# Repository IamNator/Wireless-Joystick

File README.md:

# Wireless-Joystick

Building a wireless joystick from scratch

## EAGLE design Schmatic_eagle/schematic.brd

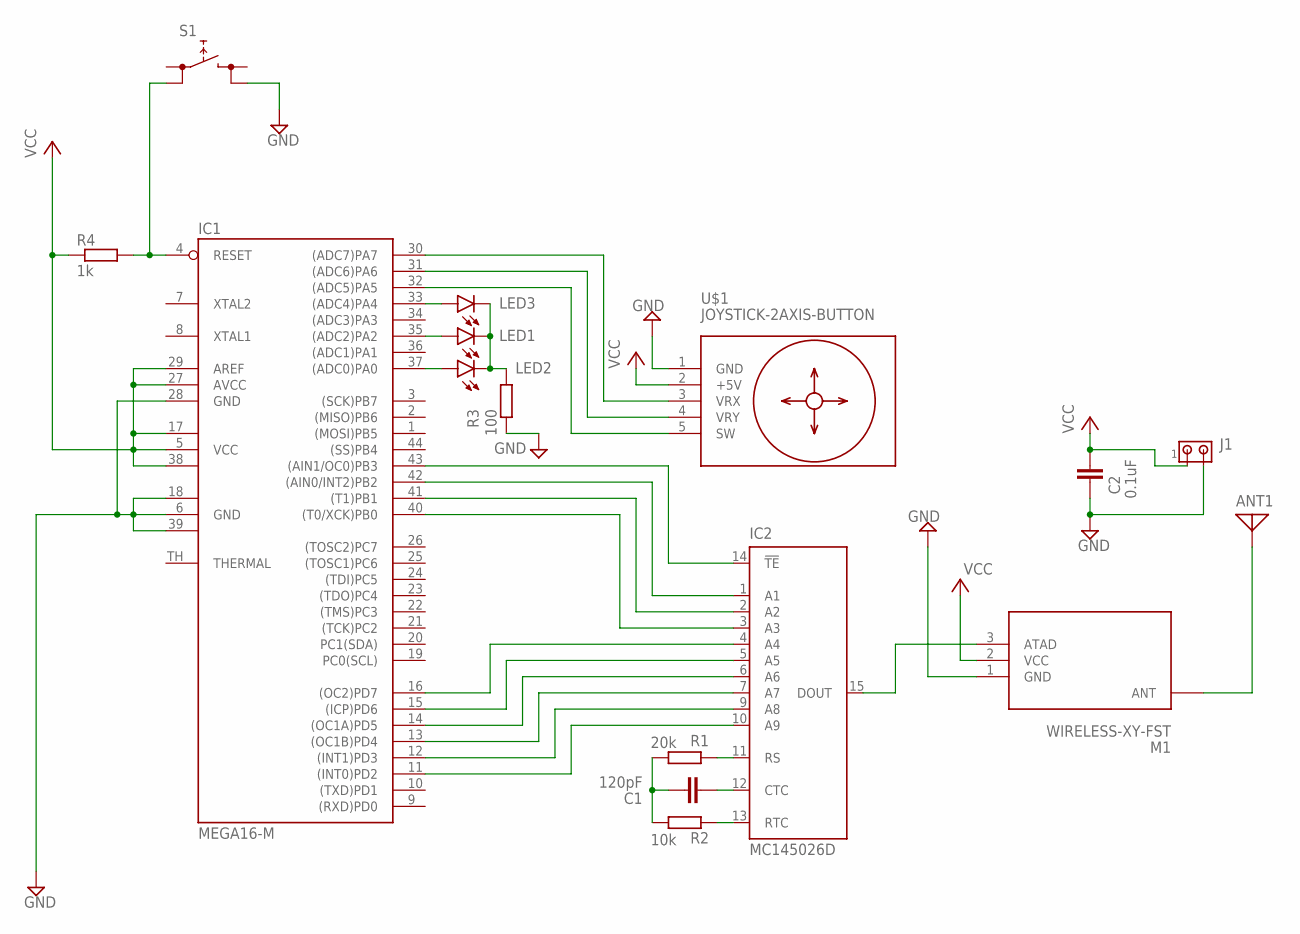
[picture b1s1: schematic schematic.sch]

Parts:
ANT1: ANTENNA; PAD-01
C1: 120pF; C2.5-3
C2: 0.1uF; C2.5-3
IC1: MEGA16-M; MLF44-TH
IC2: MC145026D; SO16
J1: MTA02-100; 10X02MTA
LED1, LED2, LED3: LEDCHIPLED_1206; CHIPLED_1206
M1: WIRELESS-XY-FST
R1: 20k; M0805
R2: 10k; R0805
R3: 100; M0805
R4: 1k; R0805
S1: REKN
U$1: JOYSTICK-2AXIS-BUTTON

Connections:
GND: C2.1, IC1.6 (GND), IC1.18 (GND1), IC1.28 (GND), IC1.39 (GND2), J1.2, M1.1 (GND), R3.2, S1.1B (1), U$1.1 (GND)
unnamed: IC1.30 ((ADC7)PA7), U$1.3 (VRX)
unnamed: IC1.31 ((ADC6)PA6), U$1.4 (VRY)
unnamed: IC1.32 ((ADC5)PA5), U$1.5 (SW)
unnamed: IC2.11 (RS), R1.1
unnamed: C1.2, IC2.12 (CTC)
unnamed: IC2.13 (RTC), R2.1
unnamed: C1.1, R1.2, R2.2
unnamed: IC2.15 (DOUT), M1.3 (ATAD)
unnamed: ANT1.1, M1.ANT
unnamed: IC1.13 ((OC1B)PD4), IC2.7 (A7)
unnamed: IC1.14 ((OC1A)PD5), IC2.6 (A6)
unnamed: IC1.15 ((ICP)PD6), IC2.5 (A5)
unnamed: IC1.11 ((INT0)PD2), IC2.10 (A9)
unnamed: IC1.12 ((INT1)PD3), IC2.9 (A8)
unnamed: IC1.16 ((OC2)PD7), IC2.4 (A4)
unnamed: IC1.4 (RESET), R4.2, S1.0B (0)
unnamed: IC1.43 ((AIN1/OC0)PB3), IC2.14 (!TE)
unnamed: IC1.42 ((AIN0/INT2)PB2), IC2.1 (A1)
unnamed: IC1.41 ((T1)PB1), IC2.2 (A2)
unnamed: IC1.40 ((T0/XCK)PB0), IC2.3 (A3)
unnamed: IC1.33 ((ADC4)PA4), LED3.A
unnamed: IC1.35 ((ADC2)PA2), LED1.A
unnamed: IC1.37 ((ADC0)PA0), LED2.A
unnamed: LED1.C, LED2.C, LED3.C, R3.1
VCC: C2.2, IC1.5 (VCC), IC1.17 (VCC1), IC1.27 (AVCC), IC1.29 (AREF), IC1.38 (VCC2), J1.1, M1.2 (VCC), R4.1, U$1.2 (+5V)
VDD: IC2.16 (VDD)
VSS: IC2.8 (VSS)

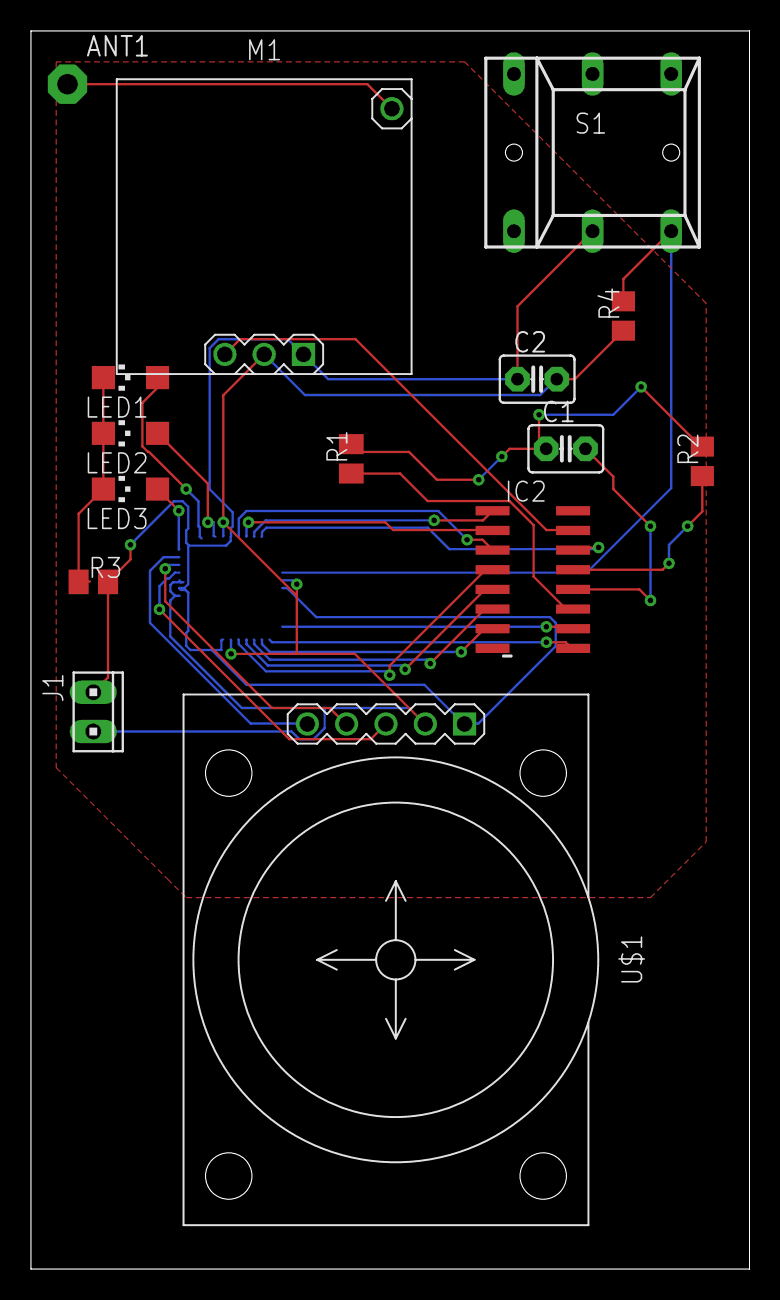
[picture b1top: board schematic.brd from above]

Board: 2 copper layers, 46.4 x 80.0 mm, 16 parts (1 on the bottom side), 26 nets.

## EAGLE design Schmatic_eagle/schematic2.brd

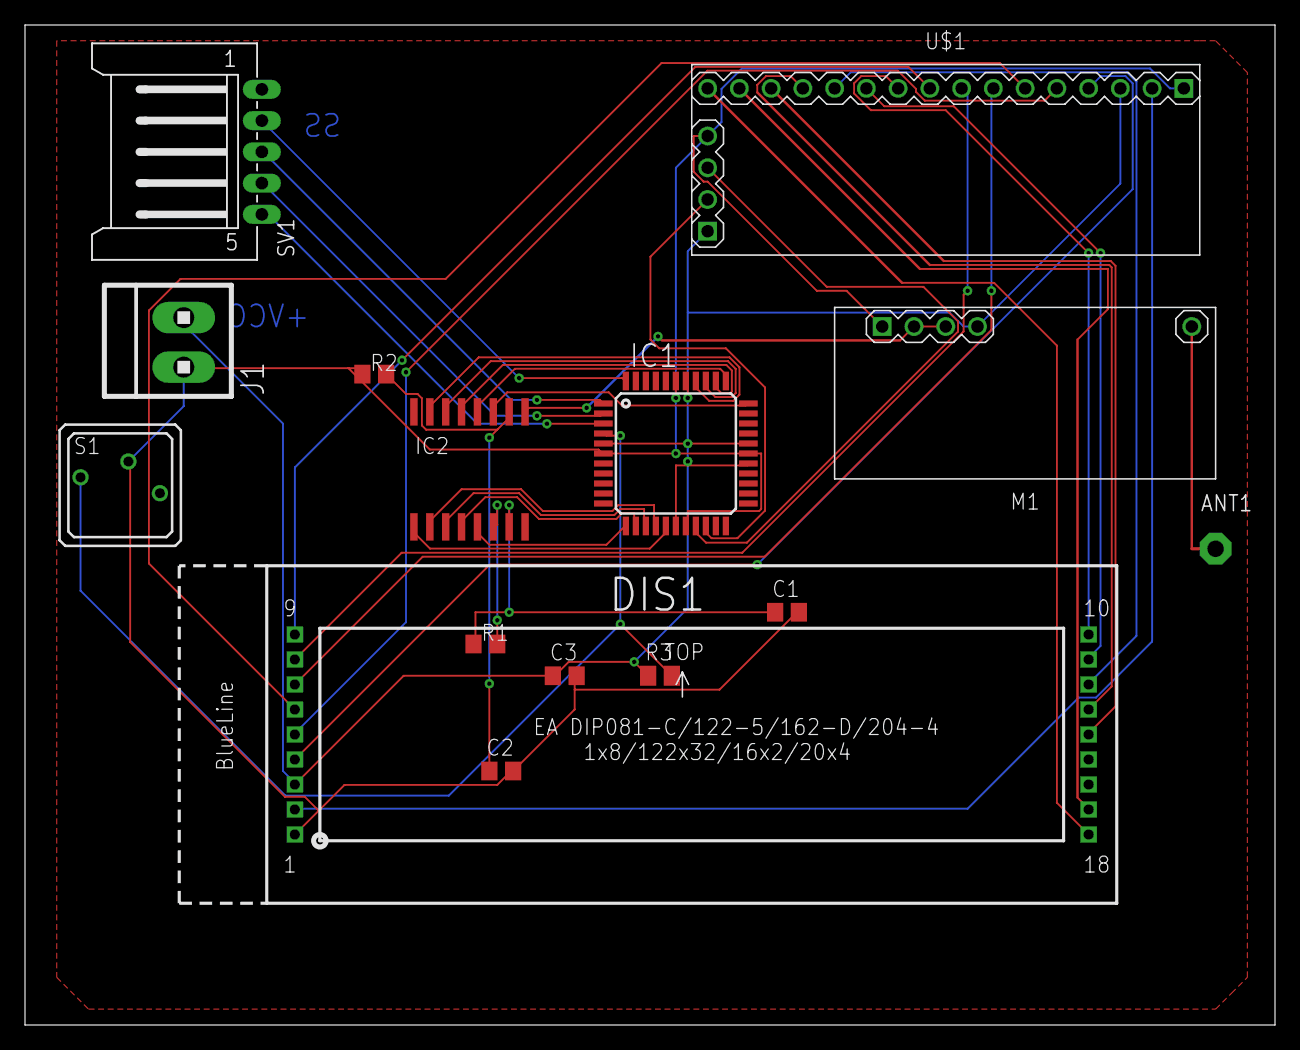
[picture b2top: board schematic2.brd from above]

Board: 2 copper layers, 100.0 x 80.0 mm, 15 parts (0 on the bottom side), 38 nets.

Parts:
ANT1: PAD-01
C1: 470pF; C0805
C2: 910pF; C0805
C3: 0.1uF; C0805
DIS1: EA_DIP
IC1: MEGA16-A; TQFP44
IC2: MC145027DW; SO16W
J1: 1X2MTA
M1: WIRELESS-XY-MK-5V
R1: 10k; R0805
R2: 100k; R0805
R3: 1k; M0805
S1: RDT1034
SV1: L05P
U$1: LCD-I2C-CONVERTER

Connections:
GND: C1.2, C2.2, C3.2, DIS1.1, IC1.6, IC1.18, IC1.28, IC1.39, J1.2, M1.1, R2.1, S1.B, U$1.J1.4, U$1.J2.1
unnamed: IC1.16, IC2.1
unnamed: IC1.15, IC2.2
unnamed: IC1.14, IC2.3
unnamed: IC1.13, IC2.4
unnamed: IC1.12, IC2.5
unnamed: IC1.35, IC2.13
unnamed: IC1.37, IC2.15
unnamed: IC1.36, IC2.14
unnamed: IC1.34, IC2.12
unnamed: IC2.6, R1.2
unnamed: C1.1, IC2.7, R1.1
unnamed: C2.1, IC2.10, R2.2
unnamed: IC2.9, M1.2, M1.3
unnamed: IC1.3, SV1.5
unnamed: ANT1.1, M1.ANT
unnamed: IC1.2, SV1.4
unnamed: IC1.1, SV1.3
unnamed: IC1.44, SV1.2
unnamed: IC1.4, R3.2, S1.A1
unnamed: IC1.33, IC2.11
unnamed: IC1.19, U$1.J1.3
unnamed: IC1.20, U$1.J1.2
unnamed: DIS1.7, U$1.J2.7
unnamed: DIS1.4, U$1.J2.4
unnamed: DIS1.5, U$1.J2.5
unnamed: DIS1.6, U$1.J2.6
unnamed: DIS1.8, U$1.J2.8
unnamed: DIS1.9, U$1.J2.9
unnamed: DIS1.10, U$1.J2.10
unnamed: DIS1.11, U$1.J2.11
unnamed: DIS1.12, U$1.J2.12
unnamed: DIS1.2, U$1.J2.2
unnamed: DIS1.13, U$1.J2.13
unnamed: DIS1.17, U$1.J2.15
unnamed: DIS1.18, U$1.J2.16
unnamed: DIS1.14, U$1.J2.14
VCC: C3.1, DIS1.3, IC1.5, IC1.17, IC1.27, IC1.29, IC1.38, J1.1, M1.4, R3.1, U$1.J1.1, U$1.J2.3

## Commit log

2019-11-07 adding aschematic
2019-11-07 Removing c files
2019-11-07 adding schematric_eagle directory
2019-11-07 updated Schematic
2019-11-07 Schematic updates
2019-11-07 Schematic updtes
2019-11-08 Schematic update
2019-11-08 Schematic 2 updates
2020-01-09 Adding a License File

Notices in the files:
README.md:
License: MIT
parts and their libraries:
diy-modules: Released under the Creative Commons Attribution 4.0 International License: http://creativecommons.org/licenses/by/4.0
